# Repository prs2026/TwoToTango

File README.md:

# TwoToTango
Repository for all CAD files and sim files (RAS, OR, etc) and other files related to this project

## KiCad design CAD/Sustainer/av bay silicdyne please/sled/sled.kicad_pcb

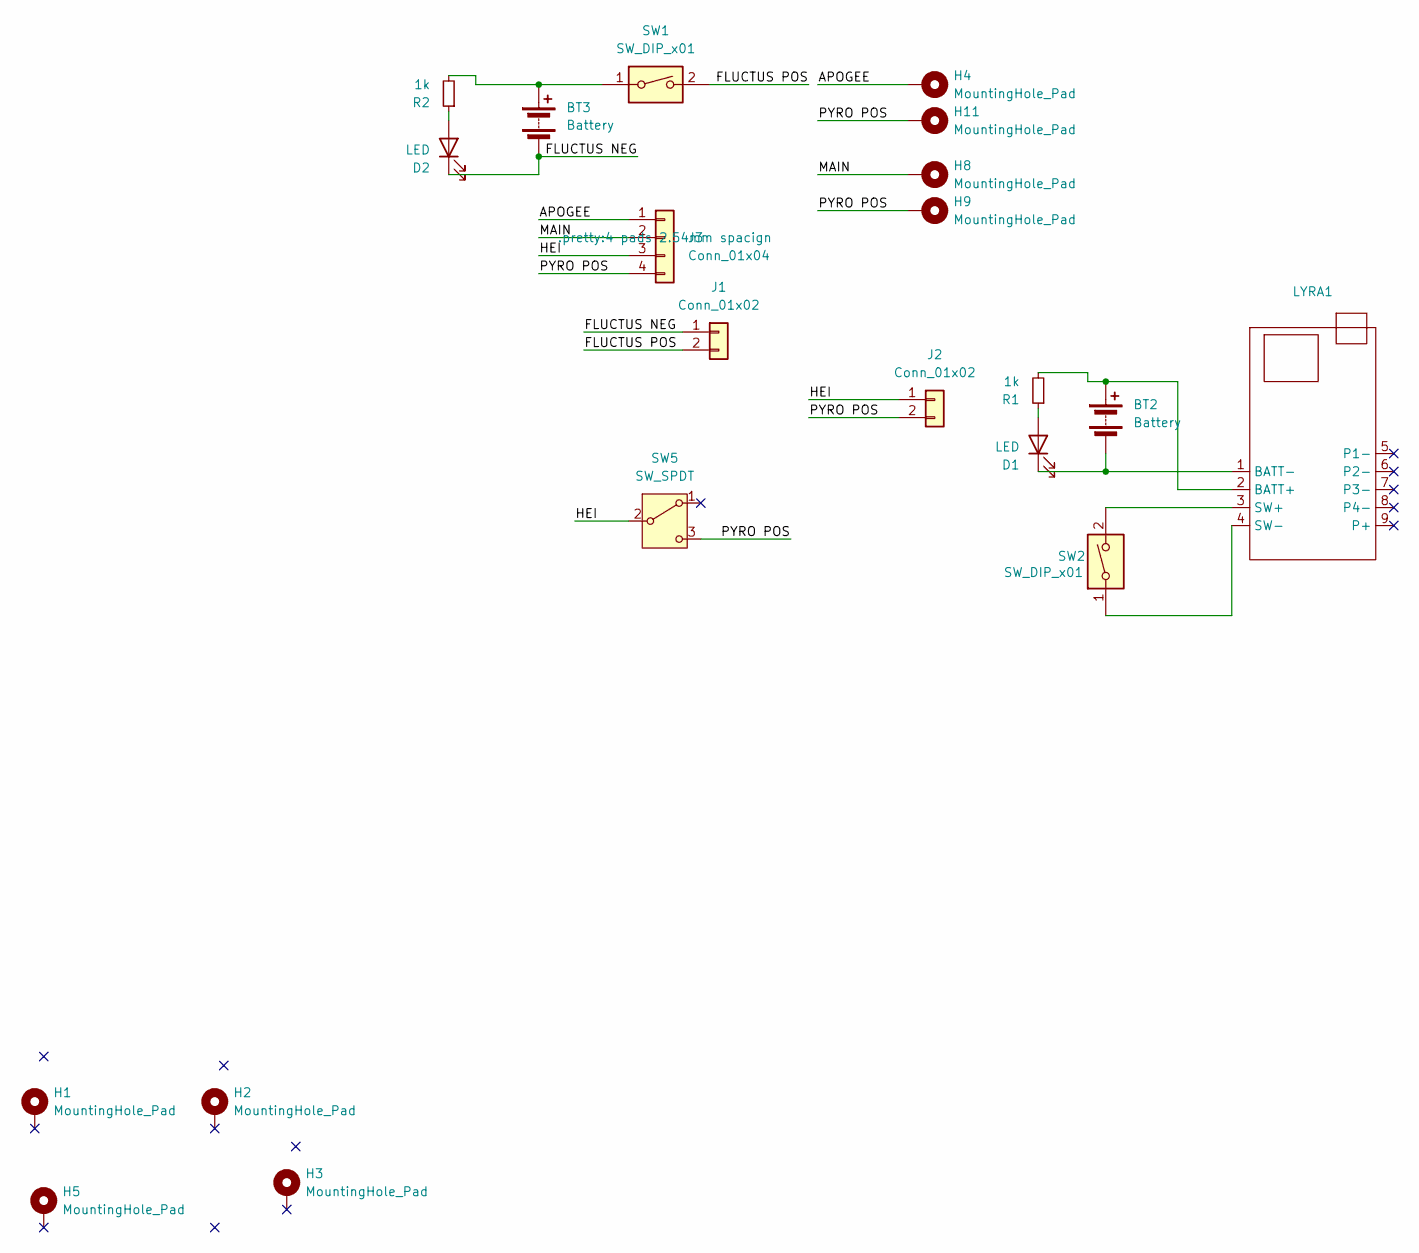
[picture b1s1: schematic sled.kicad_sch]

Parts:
BT2: Battery; PinHeader_1x02_P1.27mm_Vertical
BT3: Battery; JST_PH_B2B-PH-K_1x02_P2.00mm_Vertical
D1, D2: LED; LED_0603_1608Metric
H1, H2, H3, H5: MountingHole_Pad; MountingHole_3.2mm_M3
H4, H8, H9, H11: MountingHole_Pad; MountingHole_2.2mm_M2_DIN965_Pad
J1, J2: Conn_01x02; PinHeader_1x02_P2.54mm_Vertical
J3: Conn_01x04; 4 pads 2.54mm spacign
LYRA1: PinHeader_1x04_P2.54mm_Vertical
R1, R2: 1k; R_0603_1608Metric
SW1, SW2: SW_DIP_x01; PinHeader_1x02_P2.54mm_Vertical
SW5: SW_SPDT; TerminalBlock_bornier-3_P5.08mm

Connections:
/APOGEE: H4.1, J3.1
/FLUCTUS NEG: BT3.2 (-), D2.1 (K), J1.1
/FLUCTUS POS: J1.2, SW1.2
/HEI: J2.1, J3.3, SW5.2 (B)
/MAIN: H8.1, J3.2
/PYRO POS: H9.1, H11.1, J2.2, J3.4, SW5.3 (C)
unnamed: BT2.1 (+), LYRA1.2 (BATT+), R1.2
unnamed: BT2.2 (-), D1.1 (K), LYRA1.1 (BATT-)
unnamed: BT3.1 (+), R2.2, SW1.1
unnamed: D1.2 (A), R1.1
unnamed: D2.2 (A), R2.1
unnamed: LYRA1.3 (SW+), SW2.2
unnamed: LYRA1.4 (SW-), SW2.1

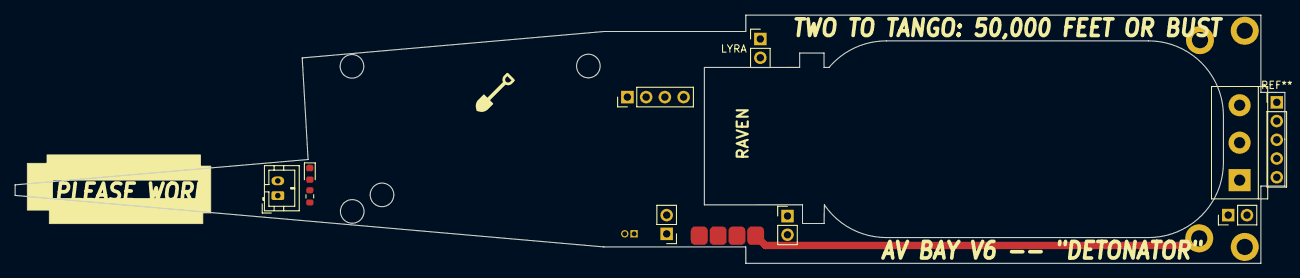
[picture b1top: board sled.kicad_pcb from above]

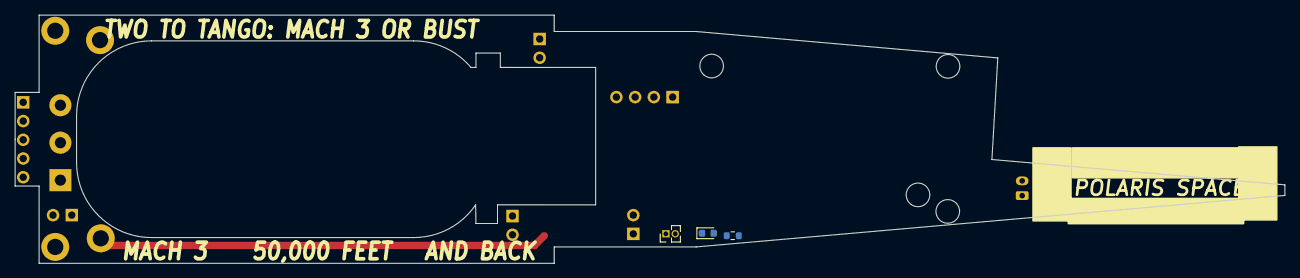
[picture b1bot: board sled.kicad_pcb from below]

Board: 2 copper layers, 172.2 x 33.7 mm, 21 parts (3 on the bottom side), 13 nets.

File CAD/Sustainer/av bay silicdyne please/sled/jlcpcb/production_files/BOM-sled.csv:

Comment,Designator,Footprint,LCSC
Battery,BT2,PinHeader_1x02_P1.27mm_Vertical,
SW_DIP_x01,SW2,PinHeader_1x02_P2.54mm_Vertical,
SW_DIP_x01,SW1,PinHeader_1x02_P2.54mm_Vertical,
~,LYRA1,PinHeader_1x04_P2.54mm_Vertical,
Conn_01x02,J2,PinHeader_1x02_P2.54mm_Vertical,
MountingHole_Pad,H11,MountingHole_2.2mm_M2_DIN965_Pad,
MountingHole_Pad,H9,MountingHole_2.2mm_M2_DIN965_Pad,
MountingHole_Pad,H8,MountingHole_2.2mm_M2_DIN965_Pad,
Battery,BT3,JST_PH_B2B-PH-K_1x02_P2.00mm_Vertical,
MountingHole_Pad,H5,MountingHole_3.2mm_M3,
MountingHole_Pad,H4,MountingHole_2.2mm_M2_DIN965_Pad,
MountingHole_Pad,H3,MountingHole_3.2mm_M3,
MountingHole_Pad,H2,MountingHole_3.2mm_M3,
MountingHole_Pad,H1,MountingHole_3.2mm_M3,
1k,R2,R_0603_1608Metric,
1k,R1,R_0603_1608Metric,
LED,D2,LED_0603_1608Metric,
LED,D1,LED_0603_1608Metric,
SW_SPDT,SW5,TerminalBlock_bornier-3_P5.08mm,
Conn_01x02,J1,PinHeader_1x02_P2.54mm_Vertical,
Conn_01x04,J3,4 pads 2.54mm spacign,

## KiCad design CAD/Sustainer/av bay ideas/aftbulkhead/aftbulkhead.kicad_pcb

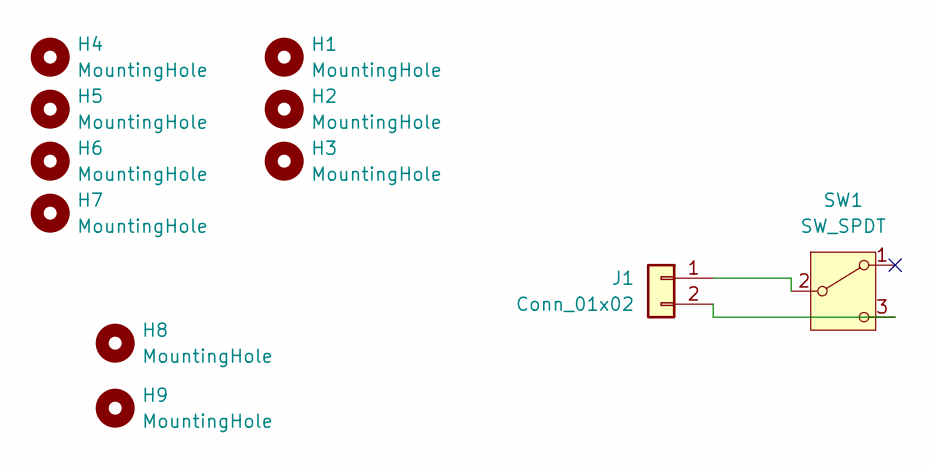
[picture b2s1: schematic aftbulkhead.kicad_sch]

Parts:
H1, H2, H3: MountingHole; MountingHole_2.2mm_M2
H4, H5, H6, H7: MountingHole; MountingHole_3.2mm_M3
H8, H9: MountingHole; MountingHole_6.4mm_M6
J1: Conn_01x02; PinHeader_1x02_P2.54mm_Vertical
SW1: SW_SPDT; TerminalBlock_bornier-3_P5.08mm

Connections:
unnamed: J1.1, SW1.2 (B)
unnamed: J1.2, SW1.3 (C)

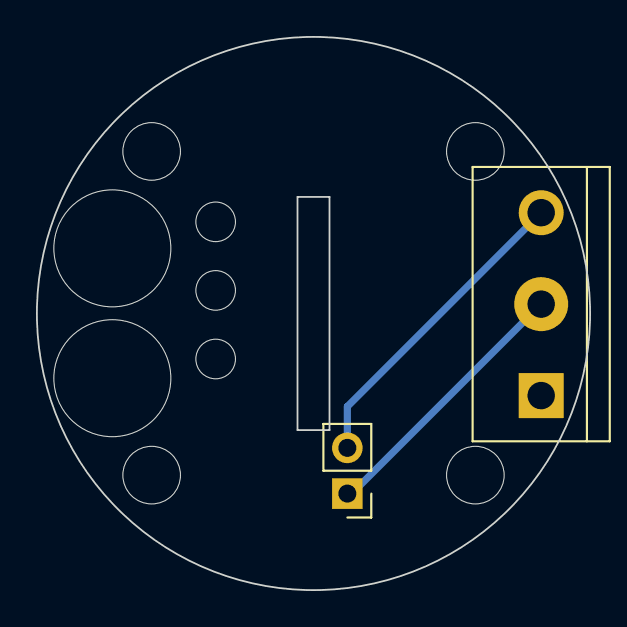
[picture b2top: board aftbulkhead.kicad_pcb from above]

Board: 2 copper layers, 30.7 x 30.7 mm, 11 parts (0 on the bottom side), 2 nets.

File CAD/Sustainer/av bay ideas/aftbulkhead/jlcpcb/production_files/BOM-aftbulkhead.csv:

Comment,Designator,Footprint,LCSC
MountingHole,H8,MountingHole_6.4mm_M6,
MountingHole,H9,MountingHole_6.4mm_M6,
MountingHole,H7,MountingHole_3.2mm_M3,
MountingHole,H6,MountingHole_3.2mm_M3,
MountingHole,H5,MountingHole_3.2mm_M3,
MountingHole,H4,MountingHole_3.2mm_M3,
MountingHole,H3,MountingHole_2.2mm_M2,
MountingHole,H2,MountingHole_2.2mm_M2,
MountingHole,H1,MountingHole_2.2mm_M2,
SW_SPDT,SW1,TerminalBlock_bornier-3_P5.08mm,
Conn_01x02,J1,PinHeader_1x02_P2.54mm_Vertical,

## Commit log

2024-07-22 init
2024-07-23 new init
2024-07-25 av bay work and finalized fin dims
2024-07-25 stuffs
2024-07-28 work, david sim init
2024-07-28 fin can work
2024-07-29 motor mount start
2024-07-30 new new new new new av bay
2024-07-31 more av bay workl
2024-07-31 built sled
2024-08-11 trip work
2024-08-12 make cablecutter
2024-08-12 work
2024-08-13 aft closure
2024-08-29 edits
2024-08-29 new sled
2024-08-30 drawings
2024-09-02 motor and mandrekl
2024-09-10 yeah
2024-09-10 silicdyn av bay
2024-09-10 cool
2024-09-12 define fins
2024-09-19 lots of work, new booster avionics bay and updates to susatiner bay
    sim work too
2024-09-24 final commit
2025-01-08 opened stuff
2025-04-01 apparently lot of edits
2025-08-26 interesting
2026-04-23 idek what changed
